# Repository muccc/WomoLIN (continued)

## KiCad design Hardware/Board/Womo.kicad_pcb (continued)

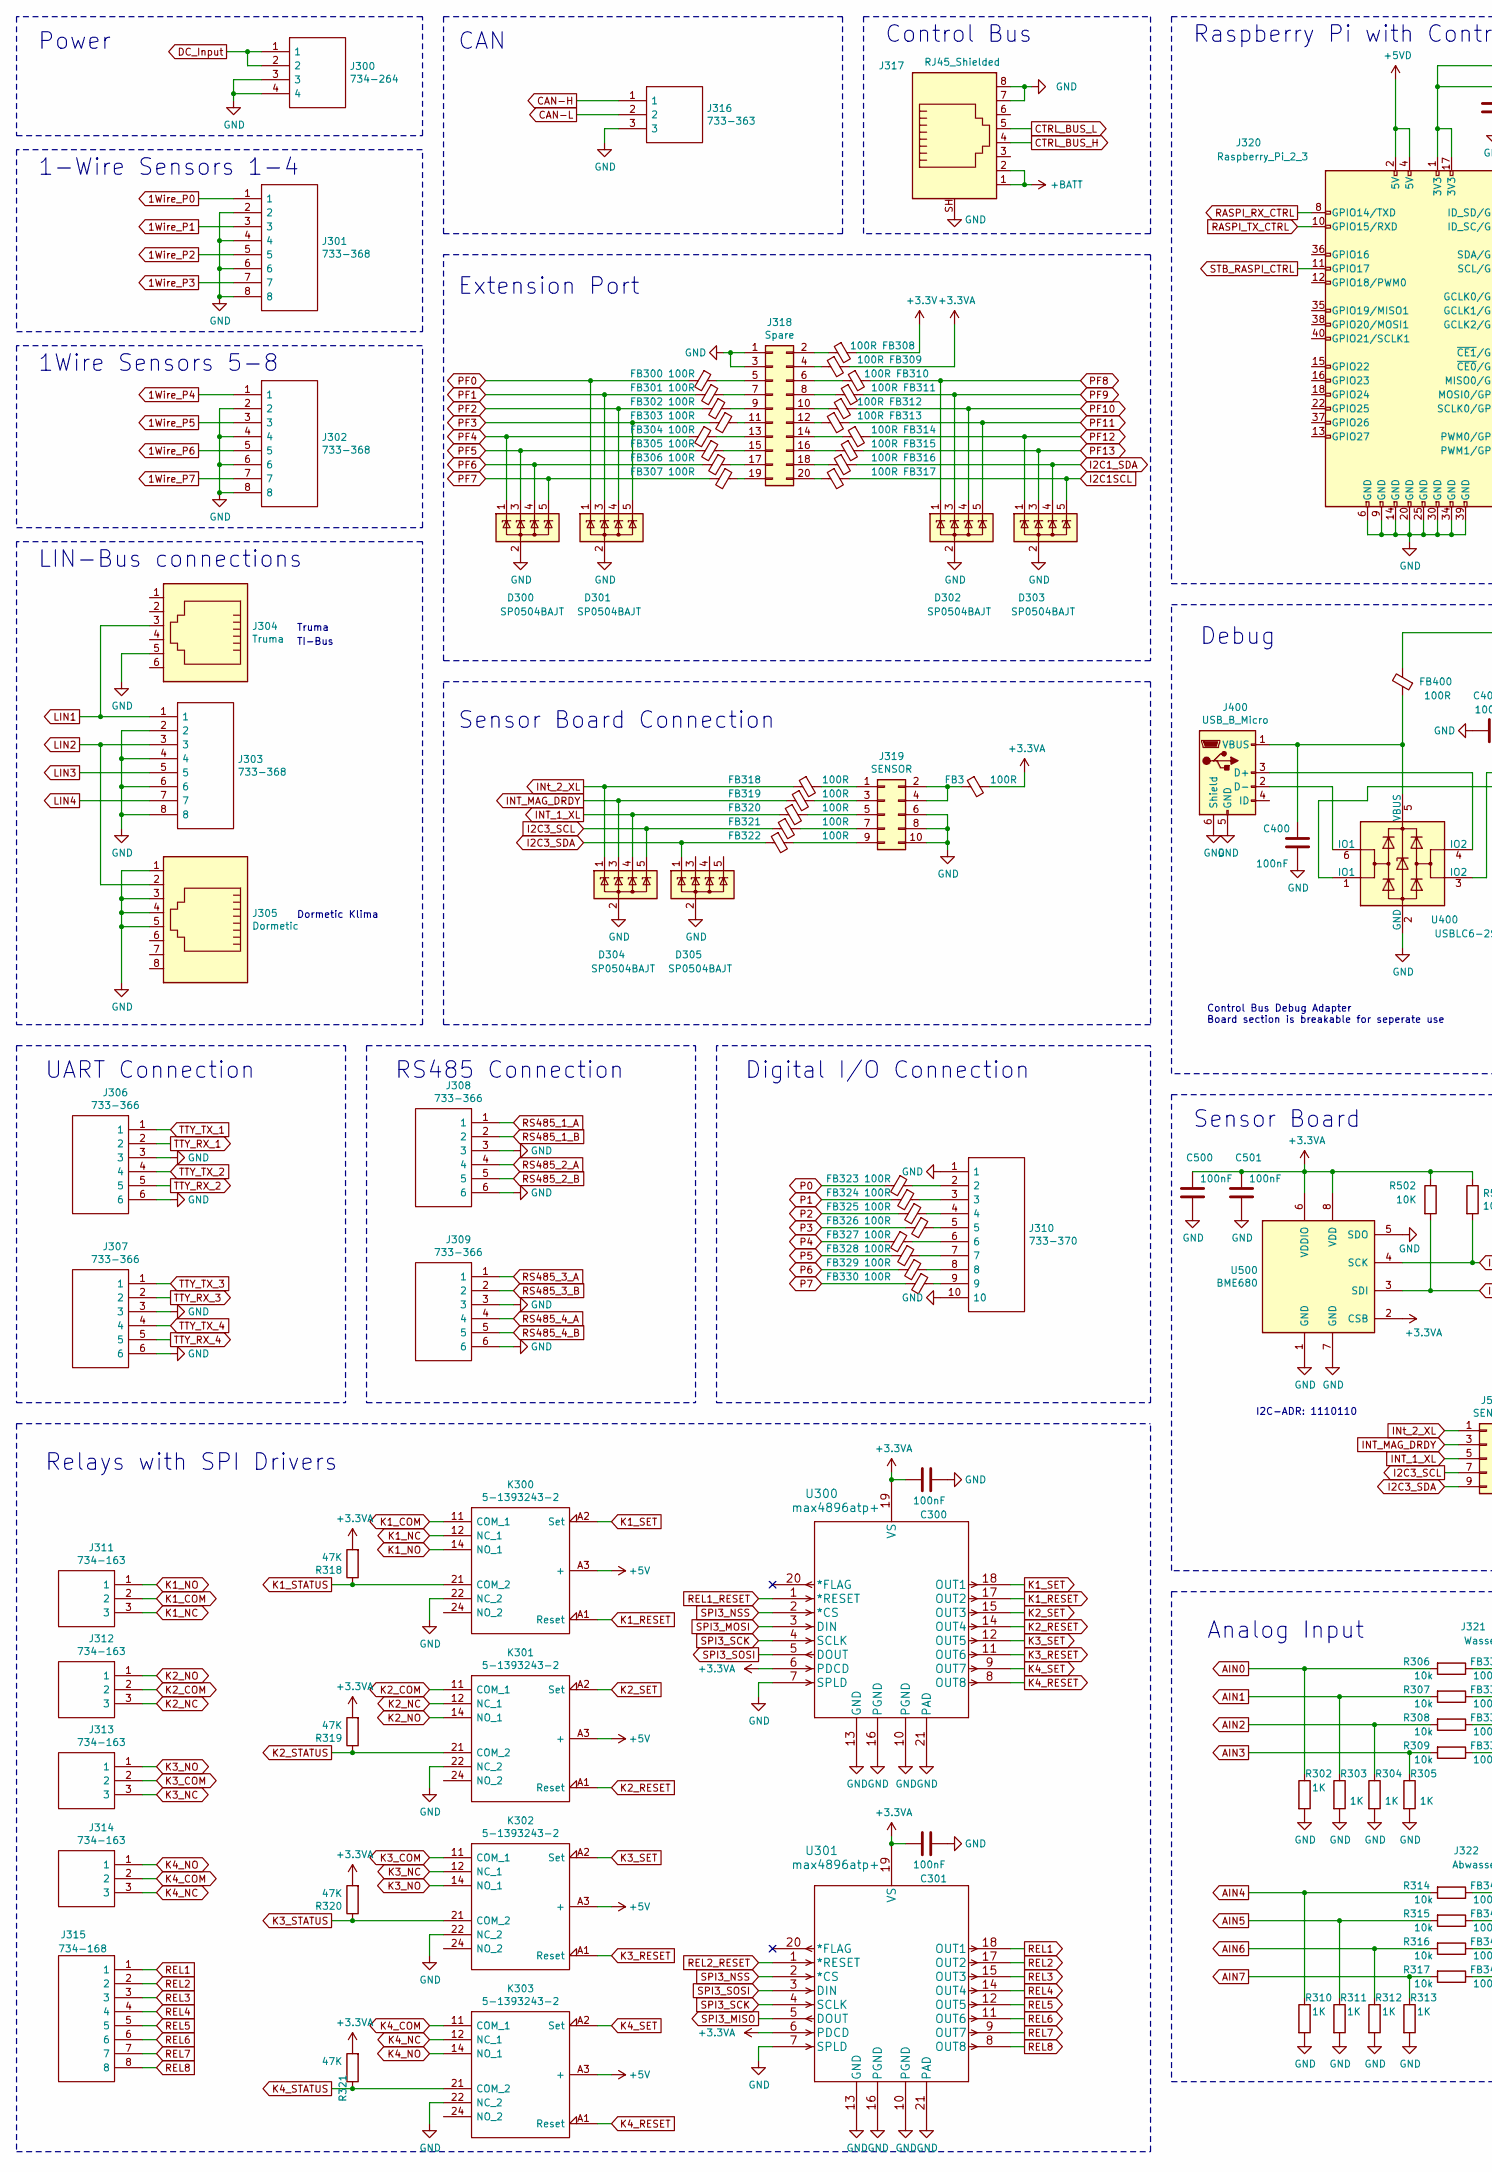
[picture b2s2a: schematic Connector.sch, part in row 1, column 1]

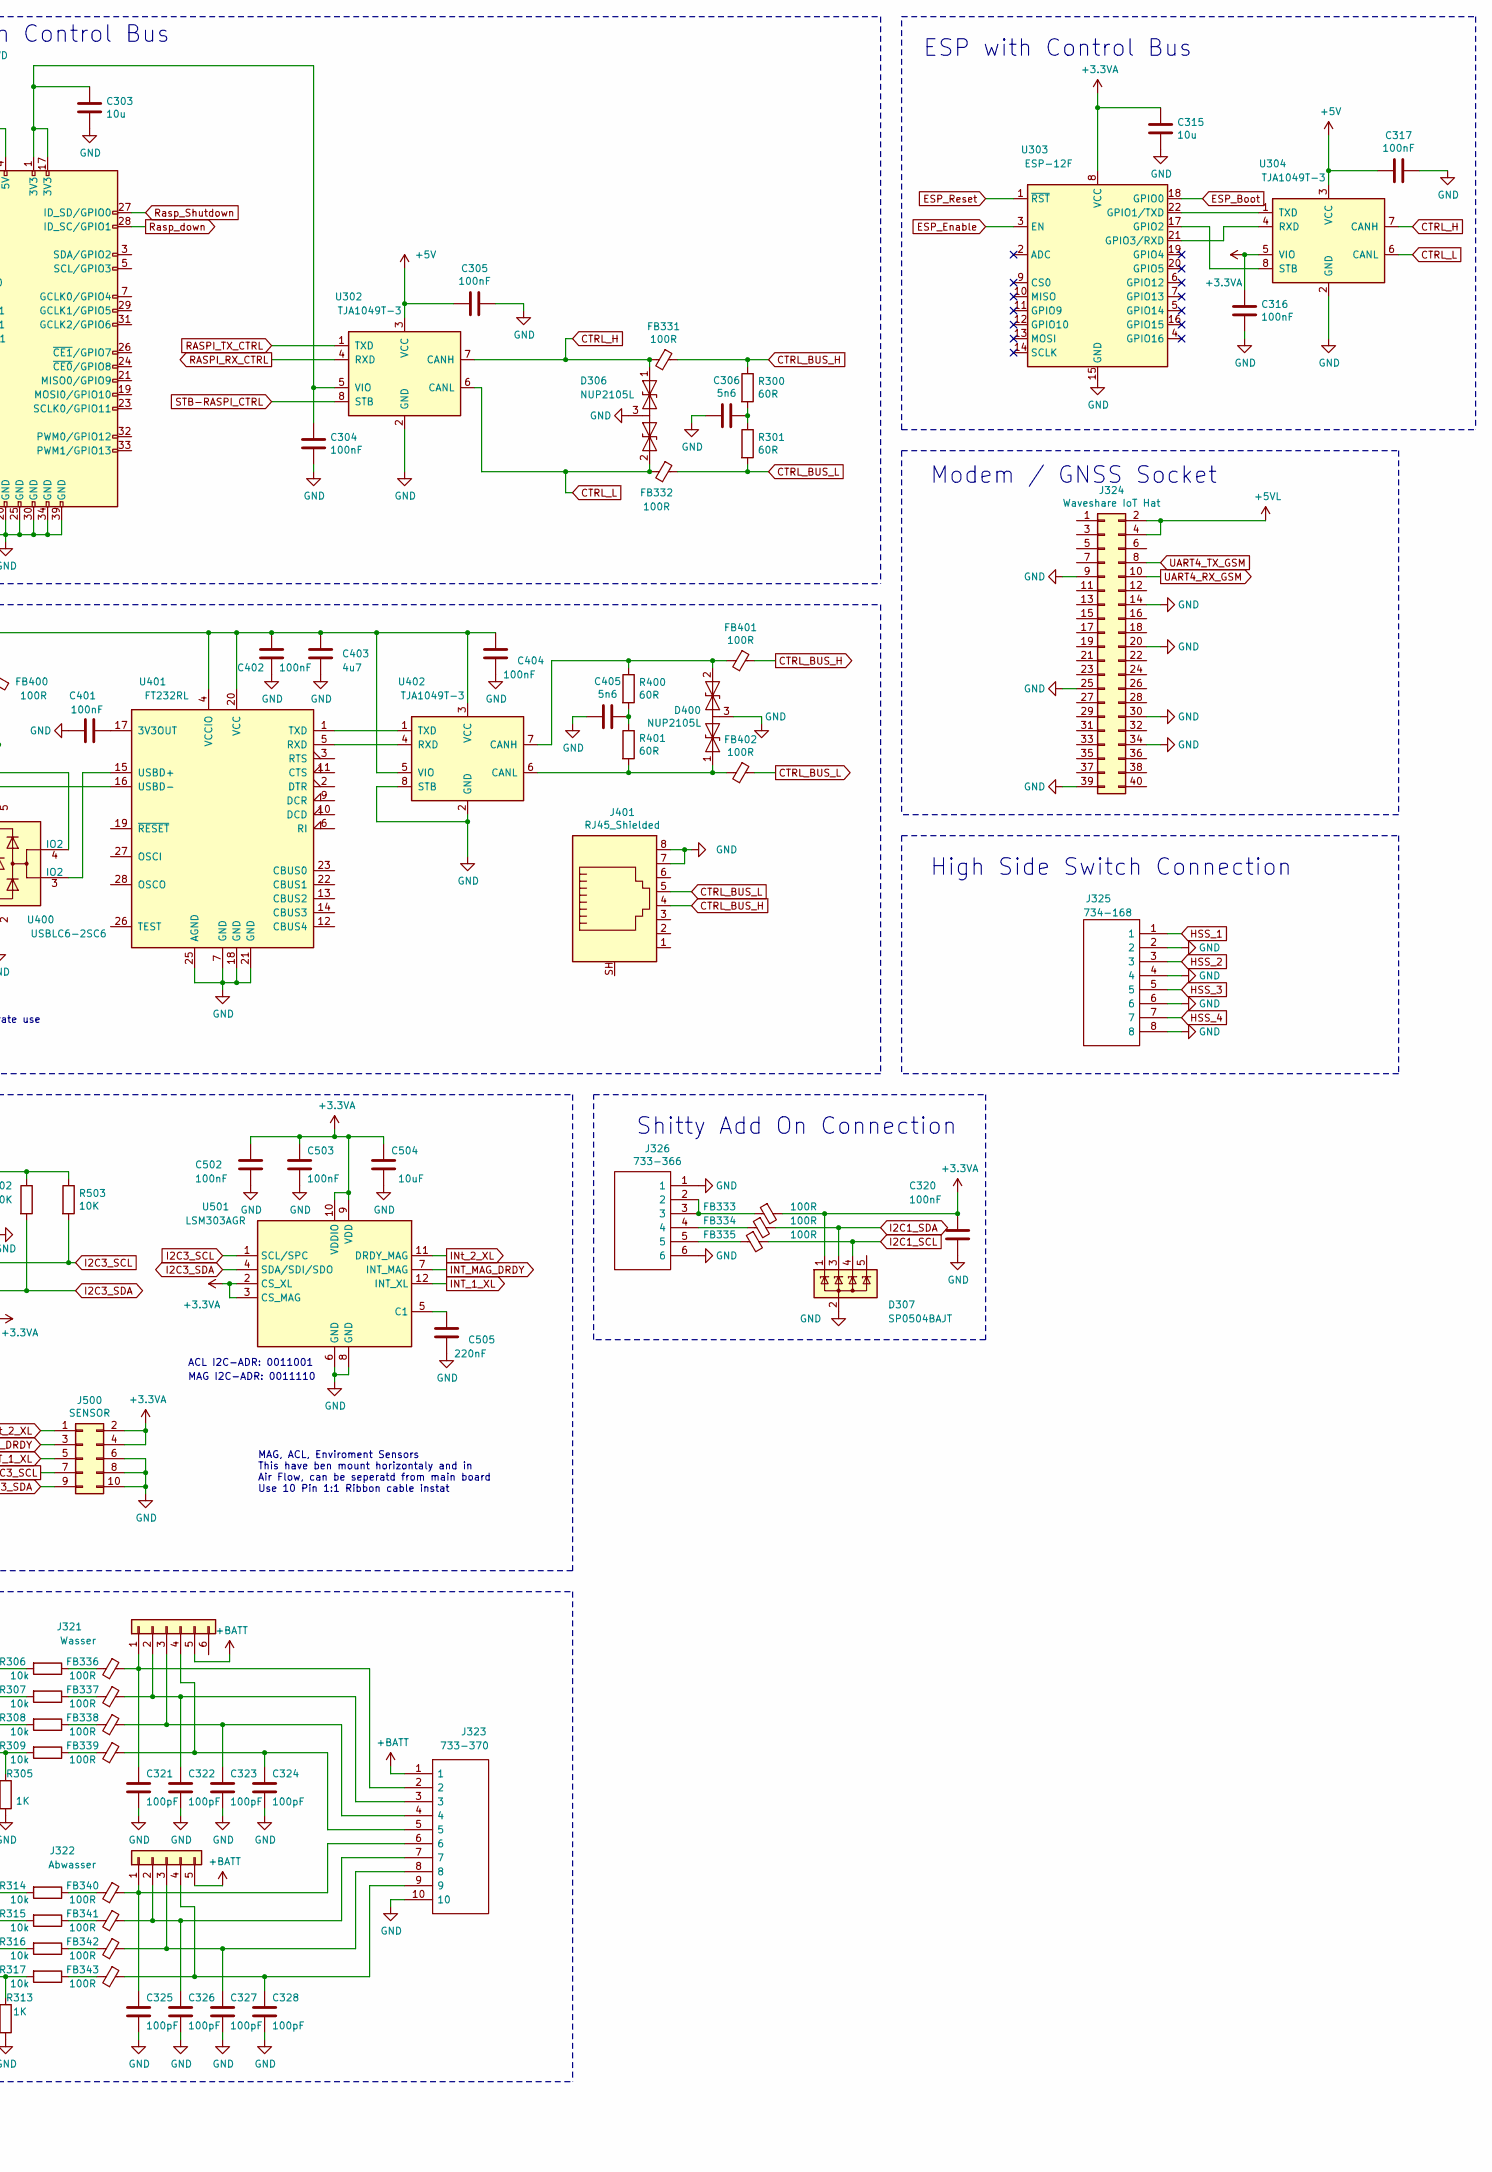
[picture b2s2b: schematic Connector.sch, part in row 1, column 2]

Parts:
C300, C301, C304, C305, C316, C317, C320, C400, C401, C402, C404, C500, C501, C502, C503: 100nF; C_0603_1608Metric
C303, C315: 10u; C_1210_3225Metric
C306, C405: 5n6; C_0603_1608Metric
C321, C322, C323, C324, C325, C326, C327, C328: 100pF; C_0603_1608Metric
C403: 4u7; C_0603_1608Metric
C504: 10uF; C_0603_1608Metric
C505: 220nF; C_0603_1608Metric
D300, D301, D302, D303, D304, D305, D307: SP0504BAJT; SOT-353_SC-70-5
D306, D400: NUP2105L; SOT-23
FB3, FB300, FB301, FB302, FB303, FB304, FB305, FB306, FB307, FB308, FB309, FB310, FB311, FB312, FB313, FB314, FB315, FB316, FB317, FB318, FB319, FB320, FB321, FB322, FB323, FB324, FB325, FB326, FB327, FB328, FB329, FB330, FB331, FB332, FB333, FB334, FB335, FB336, FB337, FB338, FB339, FB340, FB341, FB342, FB343, FB400, FB401, FB402: 100R; L_0603_1608Metric
J300: 734-264; SHDR4W120P0X381_1X4_1640X1030X850P; Manufacturer_Part_Number 734-264
J301, J302, J303: 733-368; SHDR8W80P0X250_1X8_2250X890X780P; Manufacturer_Part_Number 733-368
J304: Truma; RJ12_Amphenol_54601
J305: Dormetic; RJ45_Amphenol_54602-x08_Horizontal
J306, J307, J308, J309, J326: 733-366; SHDR6W80P0X250_1X6_1750X890X780P; Manufacturer_Part_Number 733-366
J310, J323: 733-370; SHDR10W80P0X250_1X10_2750X890X780P; Manufacturer_Part_Number 733-370
J311, J312, J313, J314: 734-163; SHDR3W100P0X350_1X3_1290X1030X850P; Manufacturer_Part_Number 734-163
J315, J325: 734-168; SHDR8W150P350X350_1X8_3040X1030X860P; Manufacturer_Part_Number 734-168
J316: 733-363; SHDR3W80P0X250_1X3_1000X890X780P; Manufacturer_Part_Number 733-363
J317, J401: RJ45_Shielded; RJ45_Amphenol_RJHSE5380
J318: Spare; PinHeader_2x10_P2.54mm_Vertical
J319, J500: SENSOR; IDC-Header_2x05_P2.54mm_Vertical
J320: Raspberry_Pi_2_3; PinSocket_2x20_P2.54mm_Vertical
J321: Wasser; 436500628
J322: Abwasser; 436500527
J324: Waveshare IoT Hat; IDC-Header_2x20_P2.54mm_Vertical
J400: USB_B_Micro; USB_Micro-B_Molex-105017-0001
K300, K301, K302, K303: 5-1393243-2; 513932432; Manufacturer_Part_Number 5-1393243-2; Mouser Part Number 655-5-1393243-2
R300, R301, R400, R401: 60R; R_0603_1608Metric
R302, R303, R304, R305, R310, R311, R312, R313: 1K; R_0603_1608Metric
R306, R307, R308, R309, R314, R315, R316, R317: 10k; R_0603_1608Metric
R318, R319, R320, R321: 47K; R_0603_1608Metric
R502, R503: 10K; R_0603_1608Metric
U300, U301: max4896atp+; max4896atp&plus_
U302, U304, U402: TJA1049T-3; SOIC-8_3.9x4.9mm_P1.27mm
U303: ESP-12F; ESP-12E
U400: USBLC6-2SC6; SOT-23-6
U401: FT232RL; SSOP-28_5.3x10.2mm_P0.65mm
U500: BME680; Bosch_LGA-8_3x3mm_P0.8mm_ClockwisePinNumbering
U501: LSM303AGR; LGA-12_2x2mm_P0.5mm

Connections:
1Wire_P0: J301.1; also elsewhere on the board
1Wire_P1: J301.3; also elsewhere on the board
1Wire_P2: J301.5; also elsewhere on the board
1Wire_P3: J301.7; also elsewhere on the board
1Wire_P4: J302.1; also elsewhere on the board
1Wire_P5: J302.3; also elsewhere on the board
1Wire_P6: J302.5; also elsewhere on the board
1Wire_P7: J302.7; also elsewhere on the board
+3.3VA: C300.2, C301.2, C315.1, C316.1, C320.1, C500.1, C501.1, C502.1, C503.1, C504.1, D307.1 (K), FB3.2, FB309.2, FB333.2, J500.2, J500.4, R318.2, R319.2, R320.2, R321.2, R502.1, R503.1, U300.6 (PDCD), U300.19 (VS), U301.6 (PDCD), U301.19 (VS), U303.8 (VCC), U304.5 (VIO), U500.2 (CSB), U500.6 (VDDIO), U500.8 (VDD), U501.2 (CS_XL), U501.3 (CS_MAG), U501.9 (VDD), U501.10 (VDDIO); also elsewhere on the board
+3V3: FB308.2; also elsewhere on the board
+5V: C305.2, C317.2, K300.A3 (+), K301.A3 (+), K302.A3 (+), K303.A3 (+), U302.3 (VCC), U304.3 (VCC); also elsewhere on the board
+5VD: J320.2 (5V), J320.4 (5V); also elsewhere on the board
+5VL: J324.2, J324.4; also elsewhere on the board
+BATT: J317.1, J317.2, J321.5, J322.5, J323.1; also elsewhere on the board
AIN0: R302.1, R306.2; also elsewhere on the board
AIN1: R303.1, R307.2; also elsewhere on the board
AIN2: R304.1, R308.2; also elsewhere on the board
AIN3: R305.1, R309.2; also elsewhere on the board
AIN4: R310.1, R314.2; also elsewhere on the board
AIN5: R311.1, R315.2; also elsewhere on the board
AIN6: R312.1, R316.2; also elsewhere on the board
AIN7: R313.1, R317.2; also elsewhere on the board
CAN-H: J316.1; also elsewhere on the board
CAN-L: J316.2; also elsewhere on the board
CTRL_BUS_H: FB331.1, FB401.1, J317.4, J401.4, R300.1
CTRL_BUS_L: FB332.1, FB402.1, J317.5, J401.5, R301.2
CTRL_H: D306.1 (A1), FB331.2, U302.7 (CANH), U304.7 (CANH); also elsewhere on the board
CTRL_L: D306.2 (A2), FB332.2, U302.6 (CANL), U304.6 (CANL); also elsewhere on the board
DC_Input: J300.1, J300.2; also elsewhere on the board
ESP_Boot: U303.18 (GPIO0); also elsewhere on the board
ESP_Enable: U303.3 (EN); also elsewhere on the board
ESP_Reset: U303.1 (~RST); also elsewhere on the board
GND: C300.1, C301.1, C303.2, C304.2, C305.1, C306.2, C315.2, C316.2, C317.1, C320.2, C321.2, C322.2, C323.2, C324.2, C325.2, C326.2, C327.2, C328.2, C400.2, C401.1, C402.2, C403.2, C404.2, C405.2, C500.2, C501.2, C502.2, C503.2, C504.2, C505.2, D300.2 (A), D301.2 (A), D302.2 (A), D303.2 (A), D304.2 (A), D305.2 (A), D306.3 (common), D307.2 (A), D400.3 (common), J300.3, J300.4, J301.2, J301.4, J301.6, J301.8, J302.2, J302.4, J302.6, J302.8, J303.2, J303.4, J303.6, J303.8, J304.5, J305.1, J305.3, J305.4, J305.5, J306.3, J306.6, J307.3, J307.6, J308.3, J308.6, J309.3, J309.6, J310.1, J310.10, J316.3, J317.7, J317.8, J317.SH, J318.1, J318.3, J319.6, J319.8, J319.10, J320.6 (GND), J320.9 (GND), J320.14 (GND), J320.20 (GND), J320.25 (GND), J320.30 (GND), J320.34 (GND), J320.39 (GND), J323.10, J324.9, J324.14, J324.20, J324.25, J324.30, J324.34, J324.39, J325.2, J325.4, J325.6, J325.8, J326.1, J326.6, J400.5 (GND), J400.6 (Shield), J401.7, J401.8, J401.SH, J500.6, J500.8, J500.10, K300.22 (NC_2), K301.22 (NC_2), K302.22 (NC_2), K303.22 (NC_2), R302.2, R303.2, R304.2, R305.2, R310.2, R311.2, R312.2, R313.2, U300.7 (SPLD), U300.10 (PGND), U300.13 (GND), U300.16 (PGND), U300.21 (PAD), U301.7 (SPLD), U301.10 (PGND), U301.13 (GND), U301.16 (PGND), U301.21 (PAD), U302.2 (GND), U303.15 (GND), U304.2 (GND), U400.2 (GND), U401.7 (GND), U401.18 (GND), U401.21 (GND), U401.25 (AGND), U402.2 (GND), U402.8 (STB), U500.1 (GND), U500.5 (SDO), U500.7 (GND), U501.6 (GND), U501.8 (GND); also elsewhere on the board
HSS_1: J325.1; also elsewhere on the board
HSS_2: J325.3; also elsewhere on the board
HSS_3: J325.5; also elsewhere on the board
HSS_4: J325.7; also elsewhere on the board
I2C1_SDA: D303.4 (K), D307.3 (K), FB316.2, FB334.2; also elsewhere on the board
I2C3_SCL: D304.5 (K), FB321.1, J500.7, R503.2, U500.4 (SCK), U501.1 (SCL/SPC); also elsewhere on the board
I2C3_SDA: D305.1 (K), FB322.1, J500.9, R502.2, U500.3 (SDI), U501.4 (SDA/SDI/SDO); also elsewhere on the board
INT_1_XL: D304.4 (K), FB320.1, J500.5, U501.12 (INT_XL); also elsewhere on the board
K1_COM: J311.2, K300.11 (COM_1)
K1_NC: J311.3, K300.12 (NC_1)
K1_NO: J311.1, K300.14 (NO_1)
K1_RESET: K300.A1 (Reset), U300.17 (OUT2)
K1_SET: K300.A2 (Set), U300.18 (OUT1)
K1_STATUS: K300.21 (COM_2), R318.1; also elsewhere on the board
K2_COM: J312.2, K301.11 (COM_1)
K2_NC: J312.3, K301.12 (NC_1)
K2_NO: J312.1, K301.14 (NO_1)
K2_RESET: K301.A1 (Reset), U300.14 (OUT4)
K2_SET: K301.A2 (Set), U300.15 (OUT3)
K2_STATUS: K301.21 (COM_2), R319.1; also elsewhere on the board
K3_COM: J313.2, K302.11 (COM_1)
K3_NC: J313.3, K302.12 (NC_1)
K3_NO: J313.1, K302.14 (NO_1)
K3_RESET: K302.A1 (Reset), U300.11 (OUT6)
K3_SET: K302.A2 (Set), U300.12 (OUT5)
K3_STATUS: K302.21 (COM_2), R320.1; also elsewhere on the board
K4_COM: J314.2, K303.11 (COM_1)
K4_NC: J314.3, K303.12 (NC_1)
K4_NO: J314.1, K303.14 (NO_1)
K4_RESET: K303.A1 (Reset), U300.8 (OUT8)
K4_SET: K303.A2 (Set), U300.9 (OUT7)
K4_STATUS: K303.21 (COM_2), R321.1; also elsewhere on the board
LIN1: J303.1, J304.3; also elsewhere on the board
LIN2: J303.3, J305.2; also elsewhere on the board
LIN3: J303.5; also elsewhere on the board
LIN4: J303.7; also elsewhere on the board
unnamed: C303.1, C304.1, J320.1 (3V3), J320.17 (3V3), U302.5 (VIO)
unnamed: C306.1, R300.2, R301.1
unnamed: C321.1, FB336.1, J321.1, J323.2
unnamed: C322.1, FB337.1, J321.2, J323.3
unnamed: C323.1, FB338.1, J321.3, J323.4
unnamed: C324.1, FB339.1, J321.4, J323.5
unnamed: C325.1, FB340.1, J322.1, J323.6
unnamed: C326.1, FB341.1, J322.2, J323.7
unnamed: C327.1, FB342.1, J322.3, J323.8
unnamed: C328.1, FB343.1, J322.4, J323.9
unnamed: C400.1, FB400.1, J400.1 (VBUS), U400.5 (VBUS)
unnamed: C401.2, U401.17 (3V3OUT)
unnamed: C402.1, C403.1, C404.1, FB400.2, U401.4 (VCCIO), U401.20 (VCC), U402.3 (VCC), U402.5 (VIO)
unnamed: C405.1, R400.2, R401.1
unnamed: C505.1, U501.5 (C1)
unnamed: D400.1 (A1), FB402.2, R401.2, U402.6 (CANL)
unnamed: D400.2 (A2), FB401.2, R400.1, U402.7 (CANH)
unnamed: FB3.1, J319.2, J319.4
unnamed: FB300.1, J318.5
unnamed: FB301.1, J318.7
unnamed: FB302.1, J318.9
unnamed: FB303.1, J318.11
unnamed: FB304.1, J318.13
unnamed: FB305.1, J318.15
unnamed: FB306.1, J318.17
unnamed: FB307.1, J318.19
unnamed: FB308.1, J318.2
unnamed: FB309.1, J318.4
unnamed: FB310.1, J318.6
unnamed: FB311.1, J318.8
unnamed: FB312.1, J318.10
unnamed: FB313.1, J318.12
unnamed: FB314.1, J318.14
unnamed: FB315.1, J318.16
unnamed: FB316.1, J318.18
unnamed: FB317.1, J318.20
unnamed: FB318.2, J319.1
unnamed: FB319.2, J319.3
unnamed: FB320.2, J319.5
unnamed: FB321.2, J319.7
unnamed: FB322.2, J319.9
unnamed: FB323.1, J310.2
unnamed: FB324.1, J310.3
unnamed: FB325.1, J310.4
unnamed: FB326.1, J310.5
unnamed: FB327.1, J310.6
unnamed: FB328.1, J310.7
unnamed: FB329.1, J310.8
unnamed: FB330.1, J310.9
unnamed: FB333.1, J326.2, J326.3
unnamed: FB334.1, J326.4
unnamed: FB335.1, J326.5
unnamed: FB336.2, R306.1
unnamed: FB337.2, R307.1
unnamed: FB338.2, R308.1
unnamed: FB339.2, R309.1
unnamed: FB340.2, R314.1
unnamed: FB341.2, R315.1
unnamed: FB342.2, R316.1
unnamed: FB343.2, R317.1
unnamed: J400.2 (D-), U400.6 (IO1)
unnamed: J400.3 (D+), U400.4 (IO2)
unnamed: U303.17 (GPIO2), U304.8 (STB)
unnamed: U303.21 (GPIO3/RXD), U304.4 (RXD)
unnamed: U303.22 (GPIO1/TXD), U304.1 (TXD)
unnamed: U400.1 (IO1), U401.16 (USBD-)
unnamed: U400.3 (IO2), U401.15 (USBD+)
unnamed: U401.1 (TXD), U402.1 (TXD)
unnamed: U401.5 (RXD), U402.4 (RXD)
P0: FB323.2; also elsewhere on the board
P1: FB324.2; also elsewhere on the board
P2: FB325.2; also elsewhere on the board
P3: FB326.2; also elsewhere on the board
P4: FB327.2; also elsewhere on the board
P5: FB328.2; also elsewhere on the board
P6: FB329.2; also elsewhere on the board
P7: FB330.2; also elsewhere on the board
PF0: D301.1 (K), FB300.2; also elsewhere on the board
PF1: D301.3 (K), FB301.2; also elsewhere on the board
PF2: D301.4 (K), FB302.2; also elsewhere on the board
PF3: D301.5 (K), FB303.2; also elsewhere on the board
PF4: D300.1 (K), FB304.2; also elsewhere on the board
PF5: D300.3 (K), FB305.2; also elsewhere on the board
PF6: D300.4 (K), FB306.2; also elsewhere on the board
PF7: D300.5 (K), FB307.2; also elsewhere on the board
PF8: D302.1 (K), FB310.2; also elsewhere on the board
PF9: D302.3 (K), FB311.2; also elsewhere on the board
PF10: D302.4 (K), FB312.2; also elsewhere on the board
PF11: D302.5 (K), FB313.2; also elsewhere on the board
PF12: D303.1 (K), FB314.2; also elsewhere on the board
PF13: D303.3 (K), FB315.2; also elsewhere on the board
RASPI_RX_CTRL: J320.8 (GPIO14/TXD), U302.4 (RXD)
RASPI_TX_CTRL: J320.10 (GPIO15/RXD), U302.1 (TXD)
REL1: J315.1, U301.18 (OUT1)
REL1_RESET: U300.1 (*RESET); also elsewhere on the board
REL2: J315.2, U301.17 (OUT2)
REL2_RESET: U301.1 (*RESET); also elsewhere on the board
REL3: J315.3, U301.15 (OUT3)
REL4: J315.4, U301.14 (OUT4)
REL5: J315.5, U301.12 (OUT5)
REL6: J315.6, U301.11 (OUT6)
REL7: J315.7, U301.9 (OUT7)
REL8: J315.8, U301.8 (OUT8)
RS485_1_A: J308.1; also elsewhere on the board
RS485_1_B: J308.2; also elsewhere on the board
RS485_2_A: J308.4; also elsewhere on the board
RS485_2_B: J308.5; also elsewhere on the board
RS485_3_A: J309.1; also elsewhere on the board
RS485_3_B: J309.2; also elsewhere on the board
RS485_4_A: J309.4; also elsewhere on the board
RS485_4_B: J309.5; also elsewhere on the board
Rasp_Shutdown: J320.27 (ID_SD/GPIO0); also elsewhere on the board
Rasp_down: J320.28 (ID_SC/GPIO1); also elsewhere on the board
SPI3_MISO: U301.5 (DOUT); also elsewhere on the board
SPI3_MOSI: U300.3 (DIN); also elsewhere on the board
SPI3_NSS: U300.2 (*CS), U301.2 (*CS); also elsewhere on the board
SPI3_SCK: U300.4 (SCLK), U301.4 (SCLK); also elsewhere on the board
SPI3_SOSI: U300.5 (DOUT), U301.3 (DIN)
STB-RASPI_CTRL: U302.8 (STB)
STB_RASPI_CTRL: J320.11 (GPIO17)
TTY_RX_1: J306.2; also elsewhere on the board
TTY_RX_2: J306.5; also elsewhere on the board
TTY_RX_3: J307.2; also elsewhere on the board
TTY_RX_4: J307.5; also elsewhere on the board
TTY_TX_1: J306.1; also elsewhere on the board
TTY_TX_2: J306.4; also elsewhere on the board
TTY_TX_3: J307.1; also elsewhere on the board
TTY_TX_4: J307.4; also elsewhere on the board
UART4_RX_GSM: J324.10; also elsewhere on the board
UART4_TX_GSM: J324.8; also elsewhere on the board

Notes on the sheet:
Truma
TI-Bus
Dormetic Klima
Power
1-Wire Sensors 1-4
1Wire Sensors 5-8
LIN-Bus connections
CAN
Control Bus Debug Adapter Board section is breakable for seperate use
I2C-ADR: 1110110
ACL I2C-ADR: 0011001
MAG I2C-ADR: 0011110
MAG, ACL, Enviroment Sensors This have ben mount horizontaly and in Air Flow, can be seperatd from main board Use 10 Pin 1:1 Ribbon cable instat
Relays with SPI Drivers
Analog Input
Debug
Sensor Board
Raspberry Pi with Control Bus
Modem / GNSS Socket
Sensor Board Connection
ESP with Control Bus
Control Bus
UART Connection
RS485 Connection
Digital I/O Connection
Extension Port
High Side Switch Connection
Shitty Add On Connection

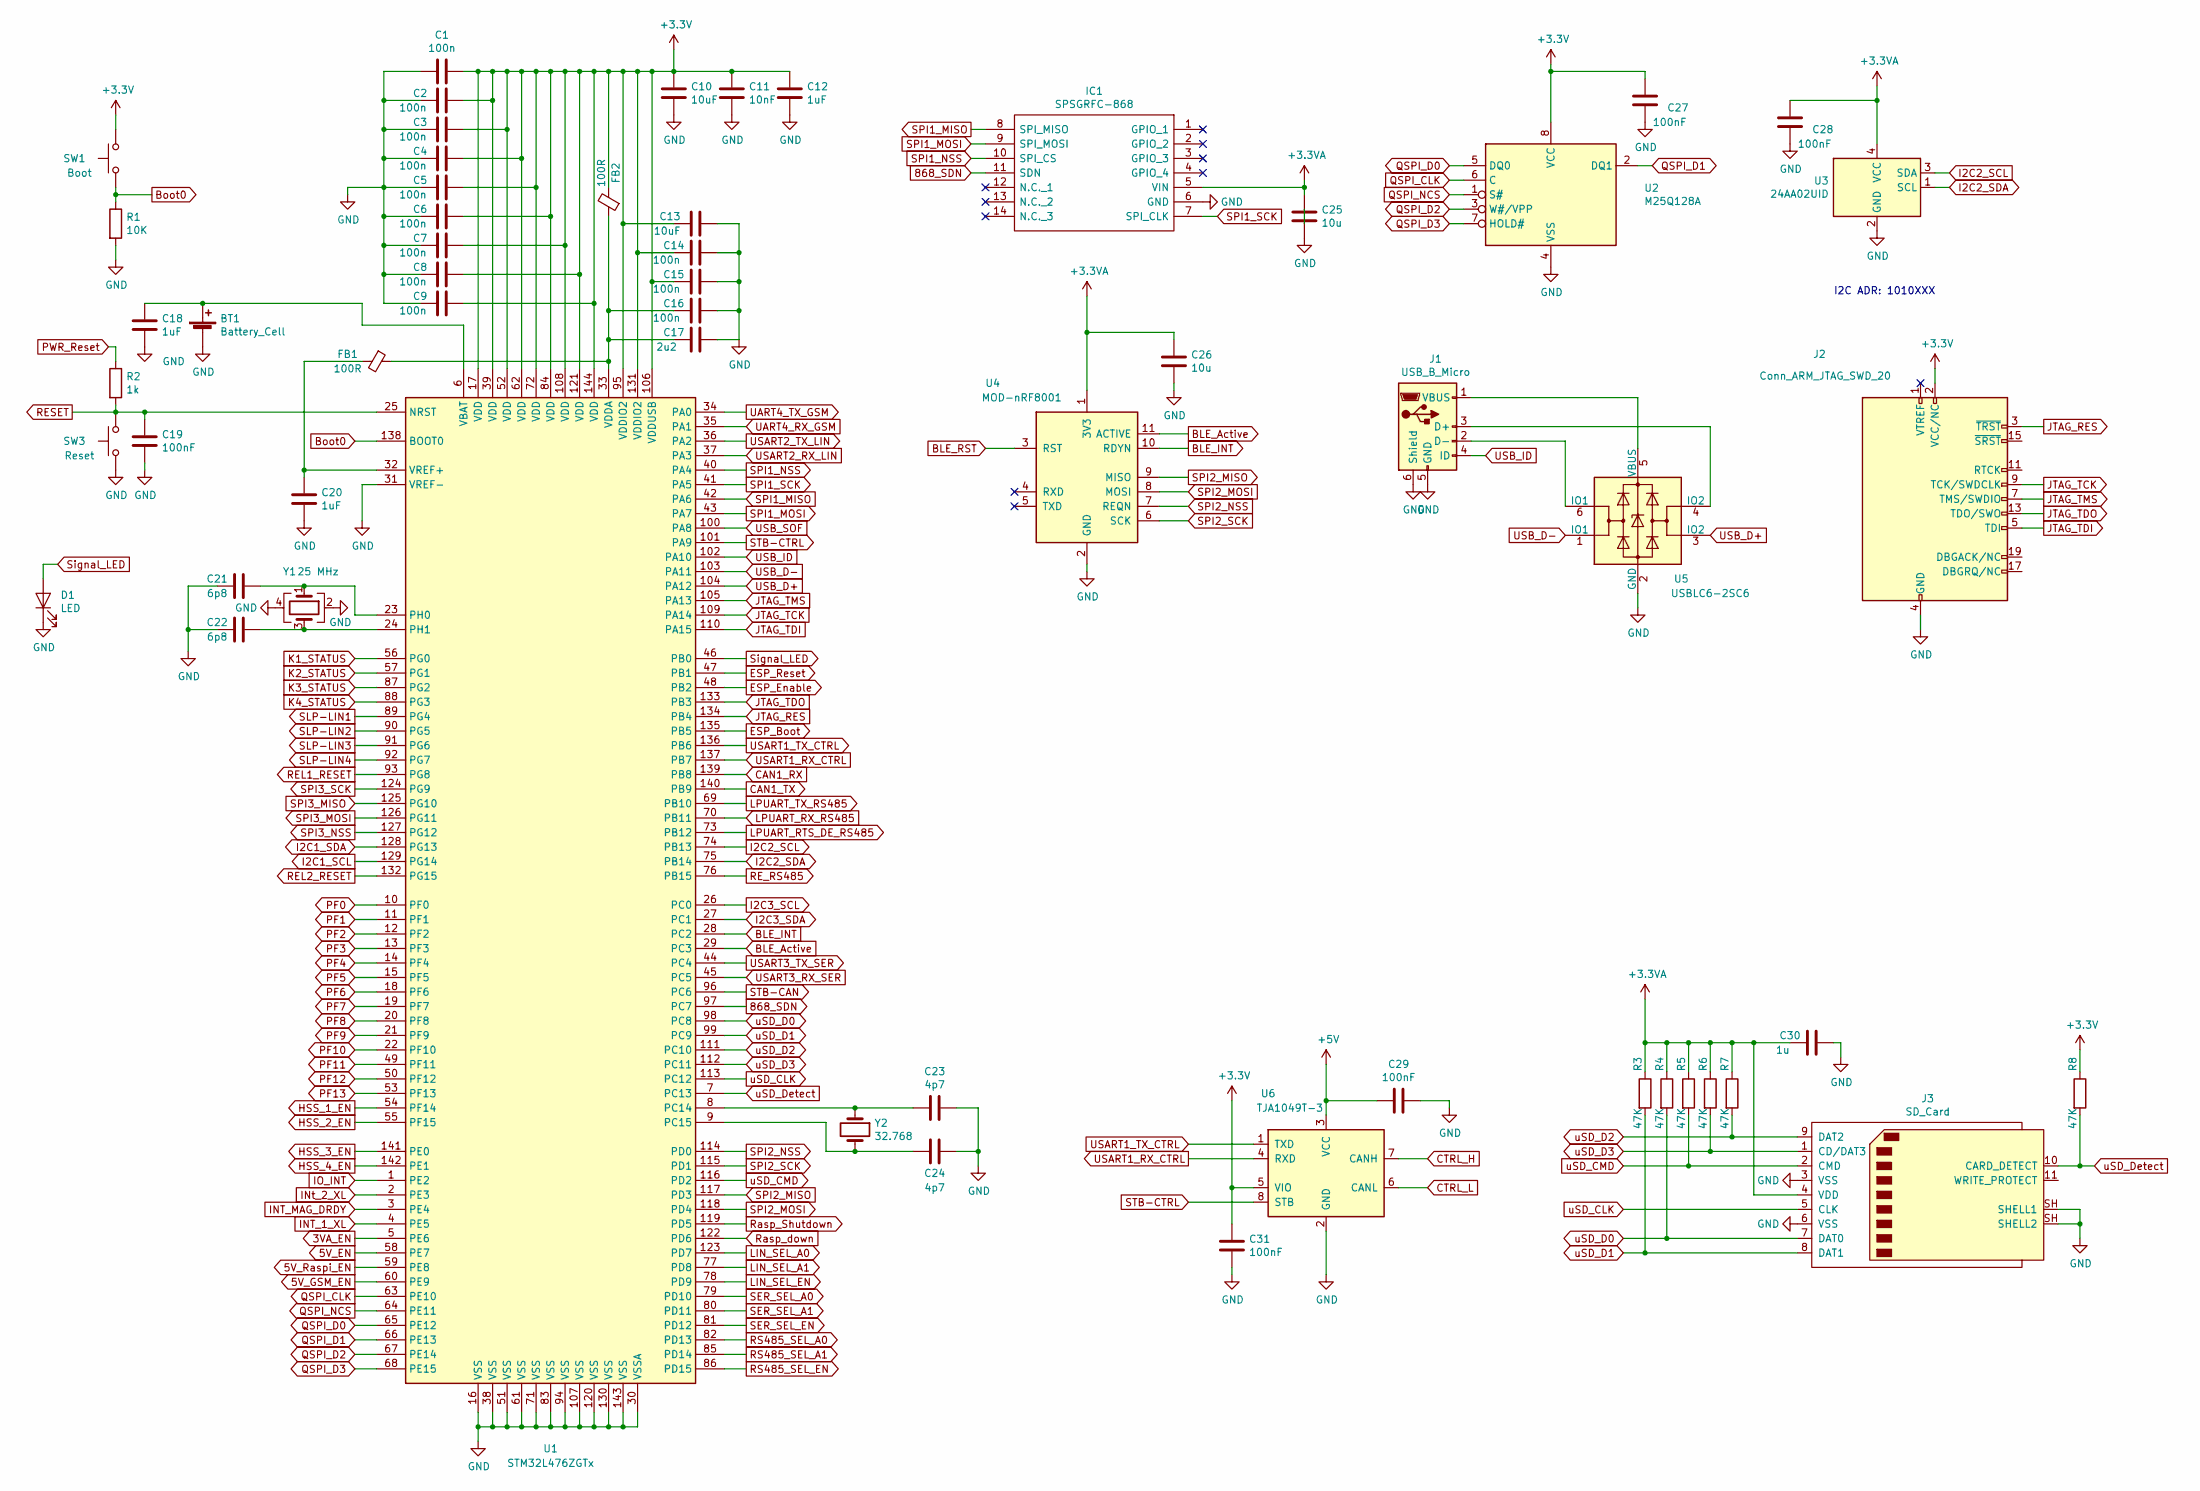
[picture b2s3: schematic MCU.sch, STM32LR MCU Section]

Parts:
BT1: Battery_Cell; BatteryHolder_Keystone_1058_1x2032
C1, C2, C3, C4, C5, C6, C7, C8, C9, C14, C15, C16: 100n; C_0603_1608Metric
C10, C13: 10uF; C_1210_3225Metric
C11: 10nF; C_0603_1608Metric
C12, C18, C20: 1uF; C_0603_1608Metric
C17: 2u2; C_1210_3225Metric
C19, C27, C28, C29, C31: 100nF; C_0603_1608Metric
C21, C22: 6p8; C_0603_1608Metric
C23, C24: 4p7; C_0603_1608Metric
C25, C26: 10u; C_1210_3225Metric
C30: 1u; C_0603_1608Metric
D1: LED; LED_1206_3216Metric
FB1, FB2: 100R; L_0603_1608Metric
IC1: SPSGRFC-868; SPSGRFC868; Manufacturer_Part_Number SPSGRFC-868; Mouser Part Number 511-SPSGRFC-868
J1: USB_B_Micro; USB_Micro-B_Molex-105017-0001
J2: Conn_ARM_JTAG_SWD_20; IDC-Header_2x10_P2.54mm_Vertical
J3: SD_Card; 10067847-001RLF
R1: 10K; R_0603_1608Metric
R2: 1k; R_0603_1608Metric
R3, R4, R5, R6, R7, R8: 47K; R_0603_1608Metric
SW1: Boot; SW_PUSH_6mm
SW3: Reset; SW_PUSH_6mm
U1: STM32L476ZGTx; LQFP-144_20x20mm_P0.5mm
U2: M25Q128A; SOIJ-8_5.3x5.3mm_P1.27mm
U3: 24AA02UID; SOT-23-5
U4: MOD-nRF8001
U5: USBLC6-2SC6; SOT-23-6
U6: TJA1049T-3; SOIC-8_3.9x4.9mm_P1.27mm
Y1: 25 MHz; Crystal_SMD_3225-4Pin_3.2x2.5mm
Y2: 32.768; Crystal_SMD_MicroCrystal_CC7V-T1A-2Pin_3.2x1.5mm

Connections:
3VA_EN: U1.5 (PE6); also elsewhere on the board
5V_EN: U1.58 (PE7); also elsewhere on the board
5V_GSM_EN: U1.60 (PE9); also elsewhere on the board
5V_Raspi_EN: U1.59 (PE8); also elsewhere on the board
868_SDN: IC1.11 (SDN), U1.97 (PC7)
+3.3VA: C25.1, C26.1, C28.1, C30.2, IC1.5 (VIN), J3.4 (VDD), R3.1, R4.1, R5.1, R6.1, R7.1, U3.4 (VCC), U4.1 (3V3); also elsewhere on the board
+3V3: C1.1, C2.1, C3.1, C4.1, C5.1, C6.1, C7.1, C8.1, C9.1, C10.1, C11.1, C12.1, C13.1, C14.2, C15.2, C27.1, C31.1, FB2.2, J2.2 (VCC/NC), R8.1, SW1.2, U1.17 (VDD), U1.39 (VDD), U1.52 (VDD), U1.62 (VDD), U1.72 (VDD), U1.84 (VDD), U1.95 (VDDIO2), U1.106 (VDDUSB), U1.108 (VDD), U1.121 (VDD), U1.131 (VDDIO2), U1.144 (VDD), U2.8 (VCC), U6.5 (VIO); also elsewhere on the board
+5V: C29.2, U6.3 (VCC); also elsewhere on the board
BLE_Active: U1.29 (PC3), U4.11 (ACTIVE)
BLE_INT: U1.28 (PC2), U4.10 (RDYN)
BLE_RST: U4.3 (RST)
Boot0: R1.1, SW1.1, U1.138 (BOOT0)
CAN1_RX: U1.139 (PB8); also elsewhere on the board
CAN1_TX: U1.140 (PB9); also elsewhere on the board
CTRL_H: U6.7 (CANH); also elsewhere on the board
CTRL_L: U6.6 (CANL); also elsewhere on the board
ESP_Boot: U1.135 (PB5); also elsewhere on the board
ESP_Enable: U1.48 (PB2); also elsewhere on the board
ESP_Reset: U1.47 (PB1); also elsewhere on the board
GND: BT1.2 (-), C1.2, C2.2, C3.2, C4.2, C5.2, C6.2, C7.2, C8.2, C9.2, C10.2, C11.2, C12.2, C13.2, C14.1, C15.1, C16.1, C17.1, C18.2, C19.2, C20.2, C21.2, C22.2, C23.1, C24.1, C25.2, C26.2, C27.2, C28.2, C29.1, C30.1, C31.2, D1.1 (K), IC1.6 (GND), J1.5 (GND), J1.6 (Shield), J2.4 (GND), J2.6 (GND), J2.8 (GND), J2.10 (GND), J2.12 (GND), J2.14 (GND), J2.16 (GND), J2.18 (GND), J2.20 (GND), J3.3 (VSS), J3.6 (VSS), J3.SH (SHELL1), R1.2, SW3.1, U1.16 (VSS), U1.30 (VSSA), U1.31 (VREF-), U1.38 (VSS), U1.51 (VSS), U1.61 (VSS), U1.71 (VSS), U1.83 (VSS), U1.94 (VSS), U1.107 (VSS), U1.120 (VSS), U1.130 (VSS), U1.143 (VSS), U2.4 (VSS), U3.2 (GND), U4.2 (GND), U5.2 (GND), U6.2 (GND), Y1.2, Y1.4; also elsewhere on the board
HSS_1_EN: U1.54 (PF14); also elsewhere on the board
HSS_2_EN: U1.55 (PF15); also elsewhere on the board
HSS_3_EN: U1.141 (PE0); also elsewhere on the board
HSS_4_EN: U1.142 (PE1); also elsewhere on the board
I2C1_SDA: U1.128 (PG13); also elsewhere on the board
I2C2_SCL: U1.74 (PB13), U3.3 (SDA); also elsewhere on the board
I2C2_SDA: U1.75 (PB14), U3.1 (SCL); also elsewhere on the board
I2C3_SCL: U1.26 (PC0); also elsewhere on the board
I2C3_SDA: U1.27 (PC1); also elsewhere on the board
INT_1_XL: U1.4 (PE5); also elsewhere on the board
IO_INT: U1.1 (PE2); also elsewhere on the board
JTAG_RES: J2.3 (~TRST~), U1.134 (PB4)
JTAG_TCK: J2.9 (TCK/SWDCLK), U1.109 (PA14)
JTAG_TDI: J2.5 (TDI), U1.110 (PA15)
JTAG_TDO: J2.13 (TDO/SWO), U1.133 (PB3)
JTAG_TMS: J2.7 (TMS/SWDIO), U1.105 (PA13)
K1_STATUS: U1.56 (PG0); also elsewhere on the board
K2_STATUS: U1.57 (PG1); also elsewhere on the board
K3_STATUS: U1.87 (PG2); also elsewhere on the board
K4_STATUS: U1.88 (PG3); also elsewhere on the board
LIN_SEL_A0: U1.123 (PD7); also elsewhere on the board
LIN_SEL_A1: U1.77 (PD8); also elsewhere on the board
LIN_SEL_EN: U1.78 (PD9); also elsewhere on the board
LPUART_RTS_DE_RS485: U1.73 (PB12); also elsewhere on the board
LPUART_RX_RS485: U1.70 (PB11); also elsewhere on the board
LPUART_TX_RS485: U1.69 (PB10); also elsewhere on the board
unnamed: BT1.1 (+), C18.1, U1.6 (VBAT)
unnamed: C16.2, C17.2, FB1.1, FB2.1, U1.33 (VDDA)
unnamed: C20.1, FB1.2, U1.32 (VREF+)
unnamed: C21.1, U1.23 (PH0), Y1.1
unnamed: C22.1, U1.24 (PH1), Y1.3
unnamed: C23.2, U1.8 (PC14), Y2.1
unnamed: C24.2, U1.9 (PC15), Y2.2
unnamed: J1.1 (VBUS), U5.5 (VBUS)
unnamed: J1.2 (D-), U5.6 (IO1)
unnamed: J1.3 (D+), U5.4 (IO2)
PF0: U1.10 (PF0); also elsewhere on the board
PF1: U1.11 (PF1); also elsewhere on the board
PF2: U1.12 (PF2); also elsewhere on the board
PF3: U1.13 (PF3); also elsewhere on the board
PF4: U1.14 (PF4); also elsewhere on the board
PF5: U1.15 (PF5); also elsewhere on the board
PF6: U1.18 (PF6); also elsewhere on the board
PF7: U1.19 (PF7); also elsewhere on the board
PF8: U1.20 (PF8); also elsewhere on the board
PF9: U1.21 (PF9); also elsewhere on the board
PF10: U1.22 (PF10); also elsewhere on the board
PF11: U1.49 (PF11); also elsewhere on the board
PF12: U1.50 (PF12); also elsewhere on the board
PF13: U1.53 (PF13); also elsewhere on the board
PWR_Reset: R2.1; also elsewhere on the board
QSPI_CLK: U1.63 (PE10), U2.6 (C)
QSPI_D0: U1.65 (PE12), U2.5 (DQ0)
QSPI_D1: U1.66 (PE13), U2.2 (DQ1)
QSPI_D2: U1.67 (PE14), U2.3 (W#/VPP)
QSPI_D3: U1.68 (PE15), U2.7 (HOLD#)
QSPI_NCS: U1.64 (PE11), U2.1 (S#)
REL1_RESET: U1.93 (PG8); also elsewhere on the board
REL2_RESET: U1.132 (PG15); also elsewhere on the board
RESET: C19.1, R2.2, SW3.2, U1.25 (NRST)
RE_RS485: U1.76 (PB15); also elsewhere on the board
RS485_SEL_A0: U1.82 (PD13); also elsewhere on the board
RS485_SEL_A1: U1.85 (PD14); also elsewhere on the board
RS485_SEL_EN: U1.86 (PD15); also elsewhere on the board
Rasp_Shutdown: U1.119 (PD5); also elsewhere on the board
Rasp_down: U1.122 (PD6); also elsewhere on the board
SER_SEL_A0: U1.79 (PD10); also elsewhere on the board
SER_SEL_A1: U1.80 (PD11); also elsewhere on the board
SER_SEL_EN: U1.81 (PD12); also elsewhere on the board
SLP-LIN1: U1.89 (PG4); also elsewhere on the board
SLP-LIN2: U1.90 (PG5); also elsewhere on the board
SLP-LIN3: U1.91 (PG6); also elsewhere on the board
SLP-LIN4: U1.92 (PG7); also elsewhere on the board
SPI1_MISO: IC1.8 (SPI_MISO), U1.42 (PA6)
SPI1_MOSI: IC1.9 (SPI_MOSI), U1.43 (PA7)
SPI1_NSS: IC1.10 (SPI_CS), U1.40 (PA4)
SPI1_SCK: IC1.7 (SPI_CLK), U1.41 (PA5)
SPI2_MISO: U1.117 (PD3), U4.9 (MISO)
SPI2_MOSI: U1.118 (PD4), U4.8 (MOSI)
SPI2_NSS: U1.114 (PD0), U4.7 (REQN)
SPI2_SCK: U1.115 (PD1), U4.6 (SCK)
SPI3_MISO: U1.125 (PG10); also elsewhere on the board
SPI3_MOSI: U1.126 (PG11); also elsewhere on the board
SPI3_NSS: U1.127 (PG12); also elsewhere on the board
SPI3_SCK: U1.124 (PG9); also elsewhere on the board
STB-CAN: U1.96 (PC6); also elsewhere on the board
STB-CTRL: U1.101 (PA9), U6.8 (STB)
Signal_LED: D1.2 (A), U1.46 (PB0)
UART4_RX_GSM: U1.35 (PA1); also elsewhere on the board
UART4_TX_GSM: U1.34 (PA0); also elsewhere on the board
USART1_RX_CTRL: U1.137 (PB7), U6.4 (RXD)
USART1_TX_CTRL: U1.136 (PB6), U6.1 (TXD)
USART2_RX_LIN: U1.37 (PA3); also elsewhere on the board
USART2_TX_LIN: U1.36 (PA2); also elsewhere on the board
USART3_RX_SER: U1.45 (PC5); also elsewhere on the board
USART3_TX_SER: U1.44 (PC4); also elsewhere on the board
USB_D+: U1.104 (PA12), U5.3 (IO2)
USB_D-: U1.103 (PA11), U5.1 (IO1)
USB_ID: J1.4 (ID), U1.102 (PA10)
USB_SOF: U1.100 (PA8)
uSD_CLK: J3.5 (CLK), U1.113 (PC12)
uSD_CMD: J3.2 (CMD), R5.2, U1.116 (PD2)
uSD_D0: J3.7 (DAT0), R4.2, U1.98 (PC8)
uSD_D1: J3.8 (DAT1), R3.2, U1.99 (PC9)
uSD_D2: J3.9 (DAT2), R7.2, U1.111 (PC10)
uSD_D3: J3.1 (CD/DAT3), R6.2, U1.112 (PC11)
uSD_Detect: J3.10 (CARD_DETECT), R8.2, U1.7 (PC13)

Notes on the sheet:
I2C ADR: 1010XXX
